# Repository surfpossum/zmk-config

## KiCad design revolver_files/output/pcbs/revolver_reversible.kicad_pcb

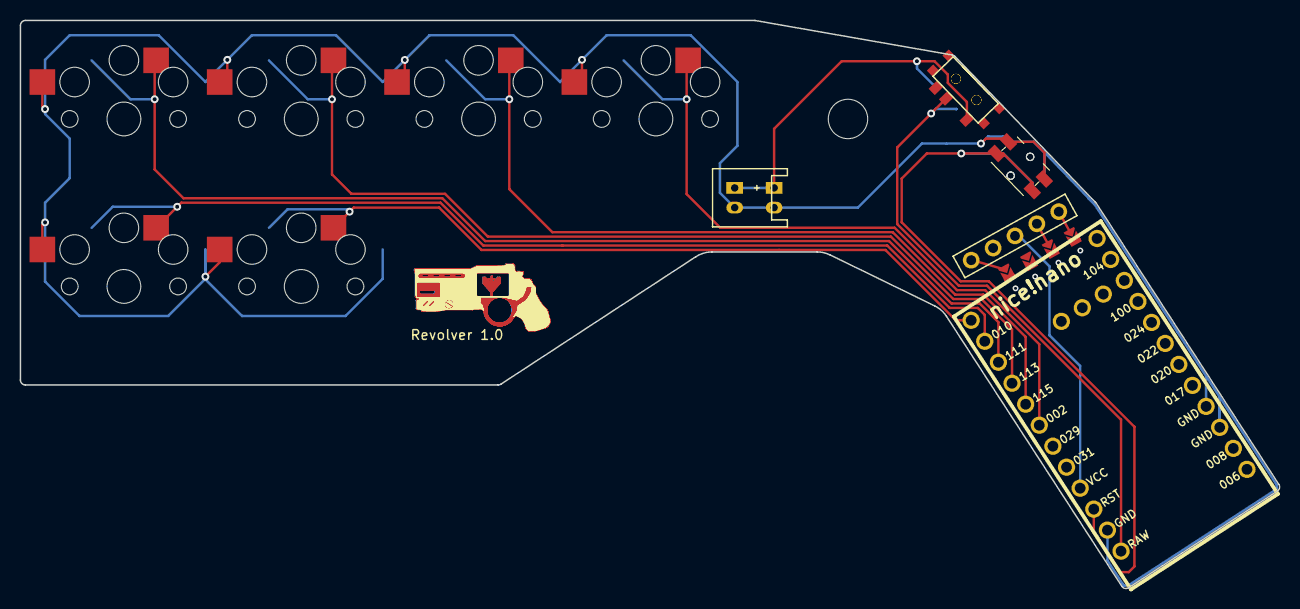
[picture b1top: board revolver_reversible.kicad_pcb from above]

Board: 2 copper layers, 127.8 x 57.7 mm, 23 parts (0 on the bottom side), 17 nets.

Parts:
B1, B2: Panasonic_EVQPUL_EVQPUC
J15, J16, J18, J18#2, J19, J20, J21, J23, J24: Jumper
JST1, JST2: JST_PH_S2B-PH-K_02x2.00mm_Angled
MCU1: nice_nano
Nice!View1: niceview_headers
S7, S8, S9, S10, S11, S12: PG1350
T1, T2: SPDT_C128955

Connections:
CS: J19.2, J20.2, J24.2
GND: B1.1, B2.1, J18.1, J18#2.2, J23.2, JST1.2, JST2.2, MCU1.3, MCU1.4, MCU1.23, S7.2, S8.2, S9.2, S10.2, S11.2, S12.2
NN_CS_SDA: J19.1, J20.1, Nice!View1.1
NN_GND_SCL: J18.2, J18#2.1, J21.1, Nice!View1.1
NN_SCL_GND: J16.1, J23.1, Nice!View1.3
NN_SDA_CS: J15.1, J24.1, Nice!View1.4
P002: MCU1.18, S12.1
P009: MCU1.13, S10.1
P010: MCU1.14, S8.1
P111: MCU1.15, S7.1
P113: MCU1.16, S9.1
P115: MCU1.17, S11.1
RAW: MCU1.24, T1.2, T2.2
RST: B1.2, B2.2, MCU1.22
SCL: J16.2, J21.2
VCC: MCU1.21, Nice!View1.2
pos: JST1.1, JST2.1, T1.1, T2.1

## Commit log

2025-02-26 Initial User Config.
2025-02-26 copying over revolver files
2025-02-26 maybe the combos are the issue now?
2025-02-26 adding CONFIG_GPIO=y to revolver.conf
2025-02-26 clearing out revolver.conf
2025-02-26 fixing erroneous / in keymap
2025-02-26 fixing structure in keymap?
2025-02-26 adding CONFIG_GPIO=y back to .conf
2025-02-26 bleh
2025-02-26 added transform stuff to .overlay
2025-02-26 added transform stuff to .dtsi instead
2025-02-26 adding ZMK_USB to .defconfig
2025-02-26 fixing keymap
2025-02-26 ...saving the .dtsi changes to keymap
2025-02-27 adding kicad and ergogen files
2025-02-27 mucking about trying to make the niceview pins reversible
2025-02-28 upping max combos
2025-02-28 fixing combo mapping
2025-02-28 messing with keymap
2025-03-05 adding fancy combo to keymap
2025-03-07 keymapping
2025-03-13 fiddling with keymap
2025-03-15 Update revolver.keymap
    Switching to ,naetor. instead of oatenris
2026-03-10 Update revolver.keymap
    updating for keycard practice
2026-03-10 Update build.yaml
    zmk updated to remove versions from board names
2026-03-10 Update build.yaml
    undoing the board naming since other stuff broke, so reverting to an older ZMK version
